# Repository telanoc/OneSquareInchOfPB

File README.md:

# OneSquareInchOfPB
ATmega328PB TQFP breakout.  This is the new chip, not the one on the Arduino
Uno.  Board design based on the "One Square Inch of Goodness" by Jeremy
Saglimbeni, found at https://github.com/jersagfast/One-Square-Inch-of-Goodness

The main difference is that this board uses the ATmega 328PB chip, which is
a bit different from the 328P used in the Arduino Uno.  I have also added a
pair of header pins for the PE0 and PE1 signals, which are handy to use for
their secondary I2C capability.  Thirdly, some capacitors on the VCC line.

Boards are already available on OSH Park at https://www.oshpark.com/shared_projects/YLrZbJlw

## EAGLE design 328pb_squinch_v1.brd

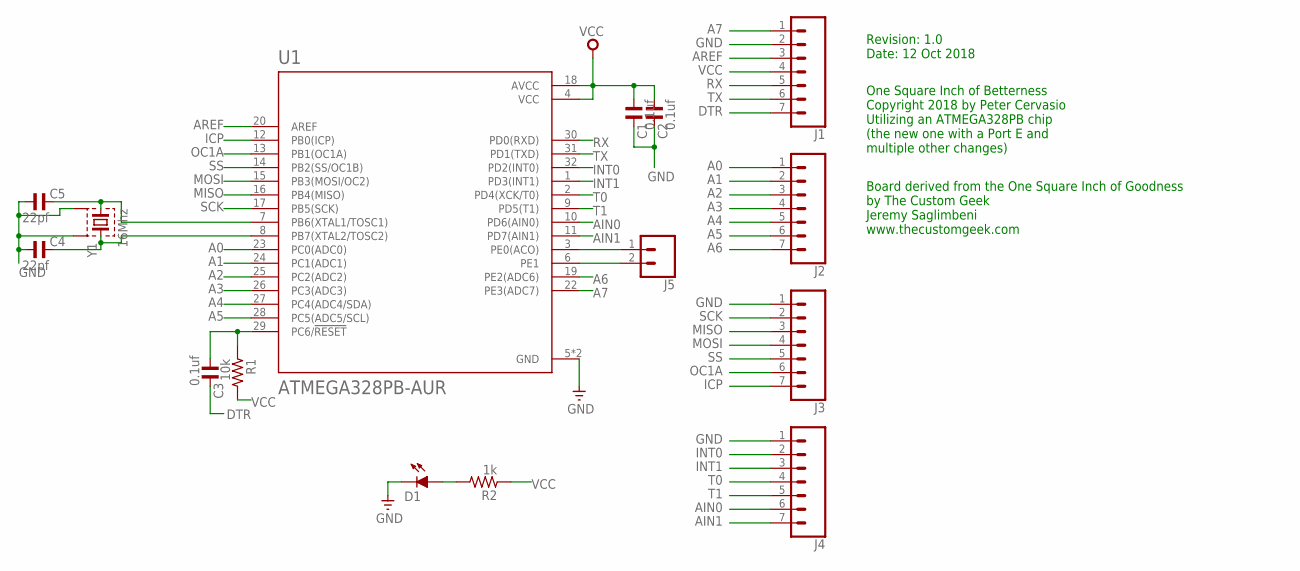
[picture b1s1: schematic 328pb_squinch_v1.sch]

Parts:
C1, C2, C3: 0.1uf; C0603
C4, C5: 22pf; C0603
D1: LEDCHIPLED_0603; CHIPLED_0603
J1, J2, J3, J4: CONN_07; 1X07
J5: CONN_02; 1X02
R1: 10k; R0603
R2: 1k; R0603
U1: ATMEGA328PB-AUR; QFP80P900X900X120-32N
Y1: 16Mhz; ABM3B

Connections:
A0: J2.1, U1.23 (PC0(ADC0))
A1: J2.2, U1.24 (PC1(ADC1))
A2: J2.3, U1.25 (PC2(ADC2))
A3: J2.4, U1.26 (PC3(ADC3))
A4: J2.5, U1.27 (PC4(ADC4/SDA))
A5: J2.6, U1.28 (PC5(ADC5/SCL))
A6: J2.7, U1.19 (PE2(ADC6))
A7: J1.1, U1.22 (PE3(ADC7))
AIN0: J4.6, U1.10 (PD6(AIN0))
AIN1: J4.7, U1.11 (PD7(AIN1))
AREF: J1.3, U1.20 (AREF)
DTR: C3.2, J1.7
GND: C1.1, C2.1, C4.1, C5.1, D1.C, J1.2, J3.1, J4.1, U1.5 (GND), U1.21 (GND), Y1.2, Y1.4
ICP: J3.7, U1.12 (PB0(ICP))
INT0: J4.2, U1.32 (PD2(INT0))
INT1: J4.3, U1.1 (PD3(INT1))
MISO: J3.3, U1.16 (PB4(MISO))
MOSI: J3.4, U1.15 (PB3(MOSI/OC2))
unnamed: C5.2, U1.7 (PB6(XTAL1/TOSC1)), Y1.1
unnamed: C4.2, U1.8 (PB7(XTAL2/TOSC2)), Y1.3
unnamed: C3.1, R1.1, U1.29 (PC6/!RESET)
unnamed: D1.A, R2.2
OC1A: J3.6, U1.13 (PB1(OC1A))
PE0: J5.1, U1.3 (PE0(ACO))
PE1: J5.2, U1.6 (PE1)
RX: J1.5, U1.30 (PD0(RXD))
SCK: J3.2, U1.17 (PB5(SCK))
SS: J3.5, U1.14 (PB2(SS/OC1B))
T0: J4.4, U1.2 (PD4(XCK/T0))
T1: J4.5, U1.9 (PD5(T1))
TX: J1.6, U1.31 (PD1(TXD))
VCC: C1.2, C2.2, J1.4, R1.2, R2.1, U1.4 (VCC), U1.18 (AVCC)

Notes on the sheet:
Board derived from the One Square Inch of Goodness by The Custom Geek Jeremy Saglimbeni www.thecustomgeek.com
One Square Inch of Betterness Copyright 2018 by Peter Cervasio Utilizing an ATMEGA328PB chip (the new one with a Port E and multiple other changes)
Revision: 1.0 Date: 12 Oct 2018

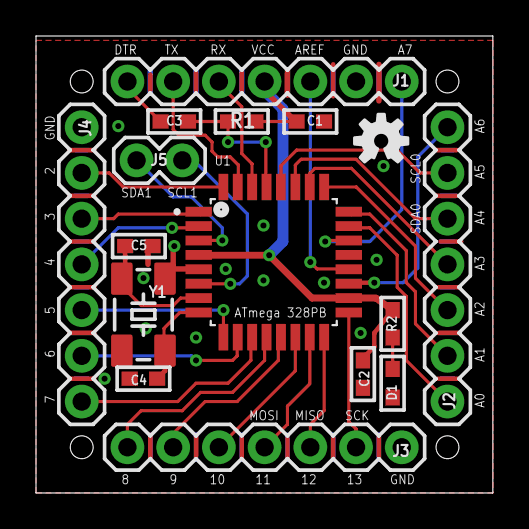
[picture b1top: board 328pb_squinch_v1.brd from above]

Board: 2 copper layers, 25.4 x 25.4 mm, 17 parts (1 on the bottom side), 32 nets.

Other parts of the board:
U$1, U$2: OSHW-LOGO-S

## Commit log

2018-10-14 Eagle files
2018-10-14 Actual readme
2018-10-14 Update with OSH Park link

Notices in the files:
parts and their libraries:
rc-master-smd: Copyright (C) 2007-2008, Bob Starr
SparkFun-Connectors: Licensing: Creative Commons ShareAlike 4.0 International - https://creativecommons.org/licenses/by-sa/4.0
